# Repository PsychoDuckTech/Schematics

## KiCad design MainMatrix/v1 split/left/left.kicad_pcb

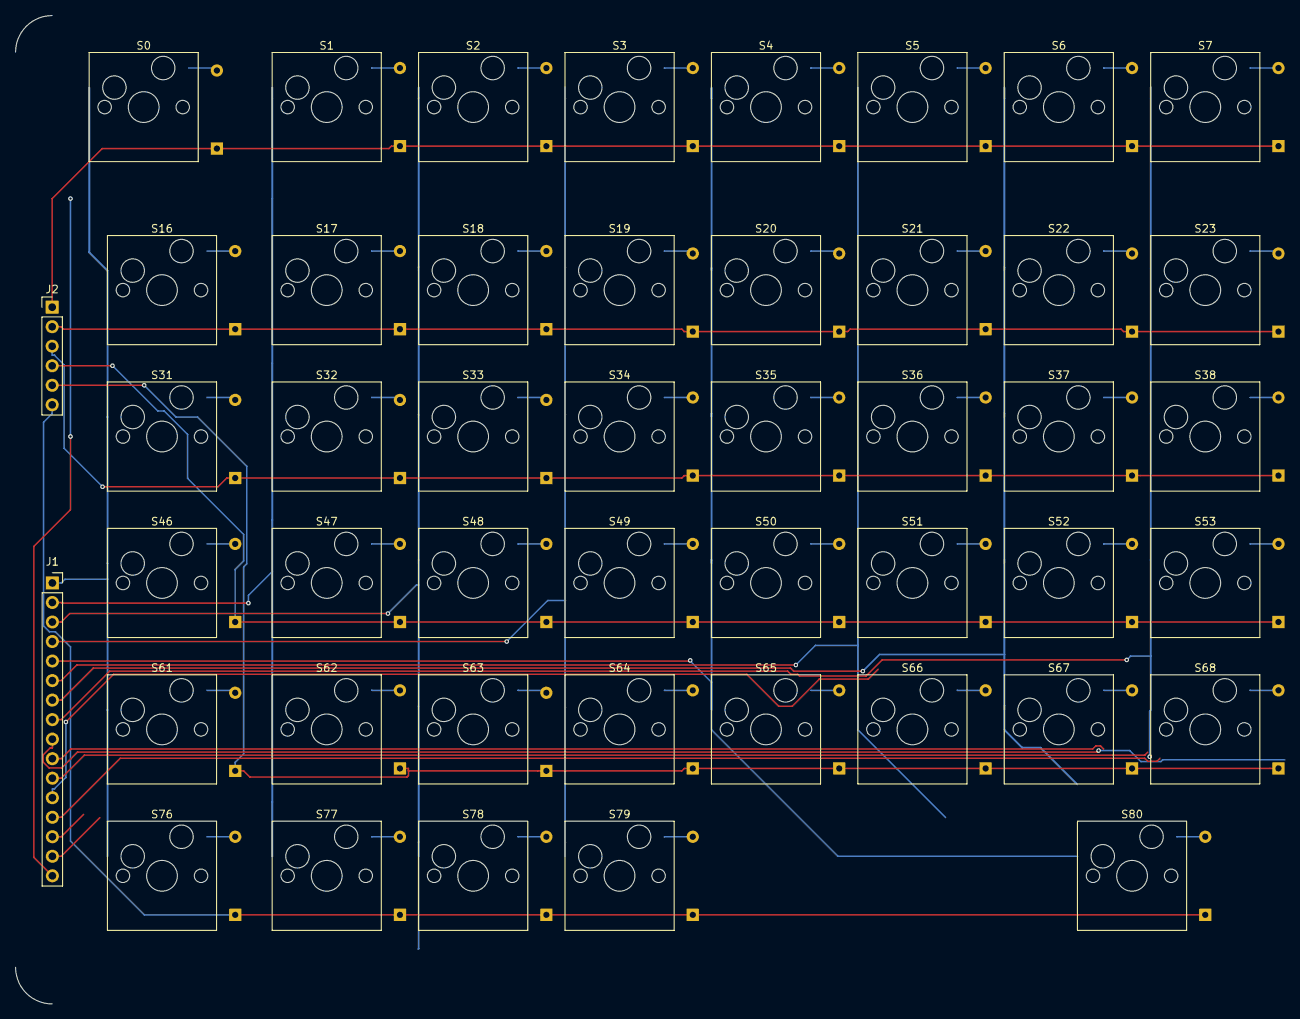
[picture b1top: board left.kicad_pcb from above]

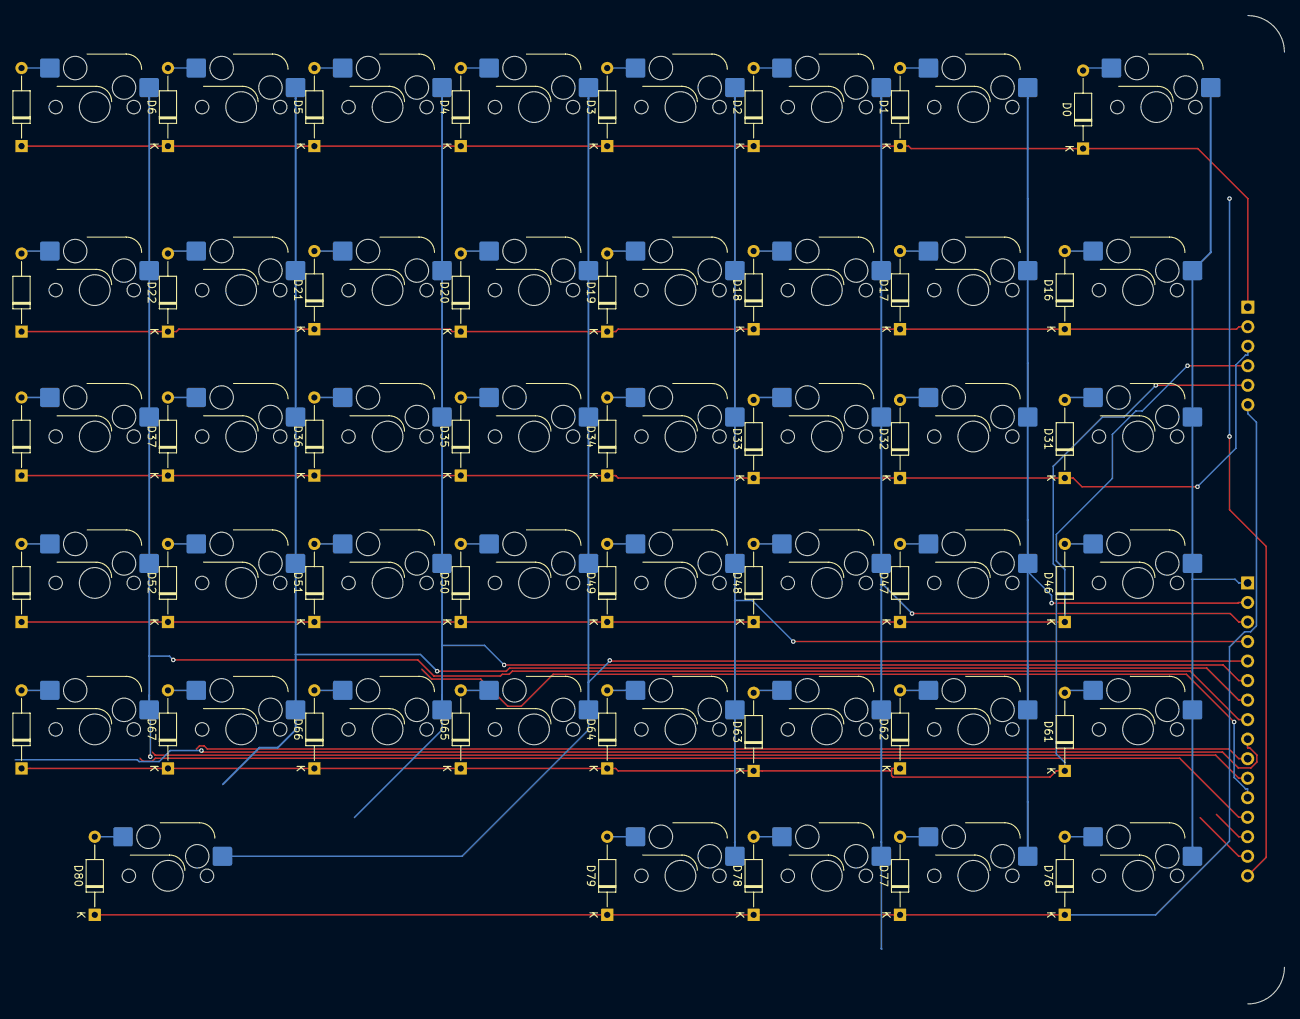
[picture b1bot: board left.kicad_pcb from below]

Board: 2 copper layers, 92 parts (45 on the bottom side), 59 nets.

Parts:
D0, D1, D2, D3, D4, D5, D6, D7, D16, D17, D18, D19, D20, D21, D22, D23, D31, D32, D33, D34, D35, D36, D37, D38, D46, D47, D48, D49, D50, D51, D52, D53, D61, D62, D63, D64, D65, D66, D67, D68, D76, D77, D78, D79, D80: Diode; D_DO-35_SOD27_P10.16mm_Horizontal
J1: Conn_01x16; PinSocket_1x16_P2.54mm_Vertical
J2: Conn_01x06; PinHeader_1x06_P2.54mm_Vertical
S0, S1, S2, S3, S4, S5, S6, S7, S16, S17, S18, S19, S20, S21, S22, S23, S31, S32, S33, S34, S35, S36, S37, S38, S46, S47, S48, S49, S50, S51, S52, S53, S61, S62, S63, S64, S65, S66, S67, S68, S76, S77, S78, S79, S80: Keyswitch; Hotswap_MX_1.00u

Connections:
/Col0: J1.1, S0.1, S16.1, S31.1, S46.1, S61.1, S76.1
/Col1: J1.2, S1.1, S17.1, S32.1, S47.1, S62.1, S77.1
/Col2: J1.3, S2.1, S18.1, S33.1, S48.1, S63.1, S78.1
/Col3: J1.4, S3.1, S19.1, S34.1, S49.1, S64.1, S79.1
/Col4: J1.5, S4.1, S20.1, S35.1, S50.1, S65.1, S80.1
/Col5: J1.6, S5.1, S21.1, S36.1, S51.1, S66.1
/Col6: J1.7, S6.1, S22.1, S37.1, S52.1, S67.1
/Col7: J1.8, S7.1, S23.1, S38.1, S53.1, S68.1
/Row0: D0.1 (K), D1.1 (K), D2.1 (K), D3.1 (K), D4.1 (K), D5.1 (K), D6.1 (K), D7.1 (K), J2.1
/Row1: D16.1 (K), D17.1 (K), D18.1 (K), D19.1 (K), D20.1 (K), D21.1 (K), D22.1 (K), D23.1 (K), J2.2
/Row2: D31.1 (K), D32.1 (K), D33.1 (K), D34.1 (K), D35.1 (K), D36.1 (K), D37.1 (K), D38.1 (K), J2.3
/Row3: D46.1 (K), D47.1 (K), D48.1 (K), D49.1 (K), D50.1 (K), D51.1 (K), D52.1 (K), D53.1 (K), J2.4
/Row4: D61.1 (K), D62.1 (K), D63.1 (K), D64.1 (K), D65.1 (K), D66.1 (K), D67.1 (K), D68.1 (K), J2.5
/Row5: D76.1 (K), D77.1 (K), D78.1 (K), D79.1 (K), D80.1 (K), J2.6
unnamed: D0.2 (A), S0.2
unnamed: D1.2 (A), S1.2
unnamed: D2.2 (A), S2.2
unnamed: D3.2 (A), S3.2
unnamed: D4.2 (A), S4.2
unnamed: D5.2 (A), S5.2
unnamed: D6.2 (A), S6.2
unnamed: D7.2 (A), S7.2
unnamed: D16.2 (A), S16.2
unnamed: D17.2 (A), S17.2
unnamed: D18.2 (A), S18.2
unnamed: D19.2 (A), S19.2
unnamed: D20.2 (A), S20.2
unnamed: D21.2 (A), S21.2
unnamed: D22.2 (A), S22.2
unnamed: D23.2 (A), S23.2
unnamed: D31.2 (A), S31.2
unnamed: D32.2 (A), S32.2
unnamed: D33.2 (A), S33.2
unnamed: D34.2 (A), S34.2
unnamed: D35.2 (A), S35.2
unnamed: D36.2 (A), S36.2
unnamed: D37.2 (A), S37.2
unnamed: D38.2 (A), S38.2
unnamed: D46.2 (A), S46.2
unnamed: D47.2 (A), S47.2
unnamed: D48.2 (A), S48.2
unnamed: D49.2 (A), S49.2
unnamed: D50.2 (A), S50.2
unnamed: D51.2 (A), S51.2
unnamed: D52.2 (A), S52.2
unnamed: D53.2 (A), S53.2
unnamed: D61.2 (A), S61.2
unnamed: D62.2 (A), S62.2
unnamed: D63.2 (A), S63.2
unnamed: D64.2 (A), S64.2
unnamed: D65.2 (A), S65.2
unnamed: D66.2 (A), S66.2
unnamed: D67.2 (A), S67.2
unnamed: D68.2 (A), S68.2
unnamed: D76.2 (A), S76.2
unnamed: D77.2 (A), S77.2
unnamed: D78.2 (A), S78.2
unnamed: D79.2 (A), S79.2
unnamed: D80.2 (A), S80.2

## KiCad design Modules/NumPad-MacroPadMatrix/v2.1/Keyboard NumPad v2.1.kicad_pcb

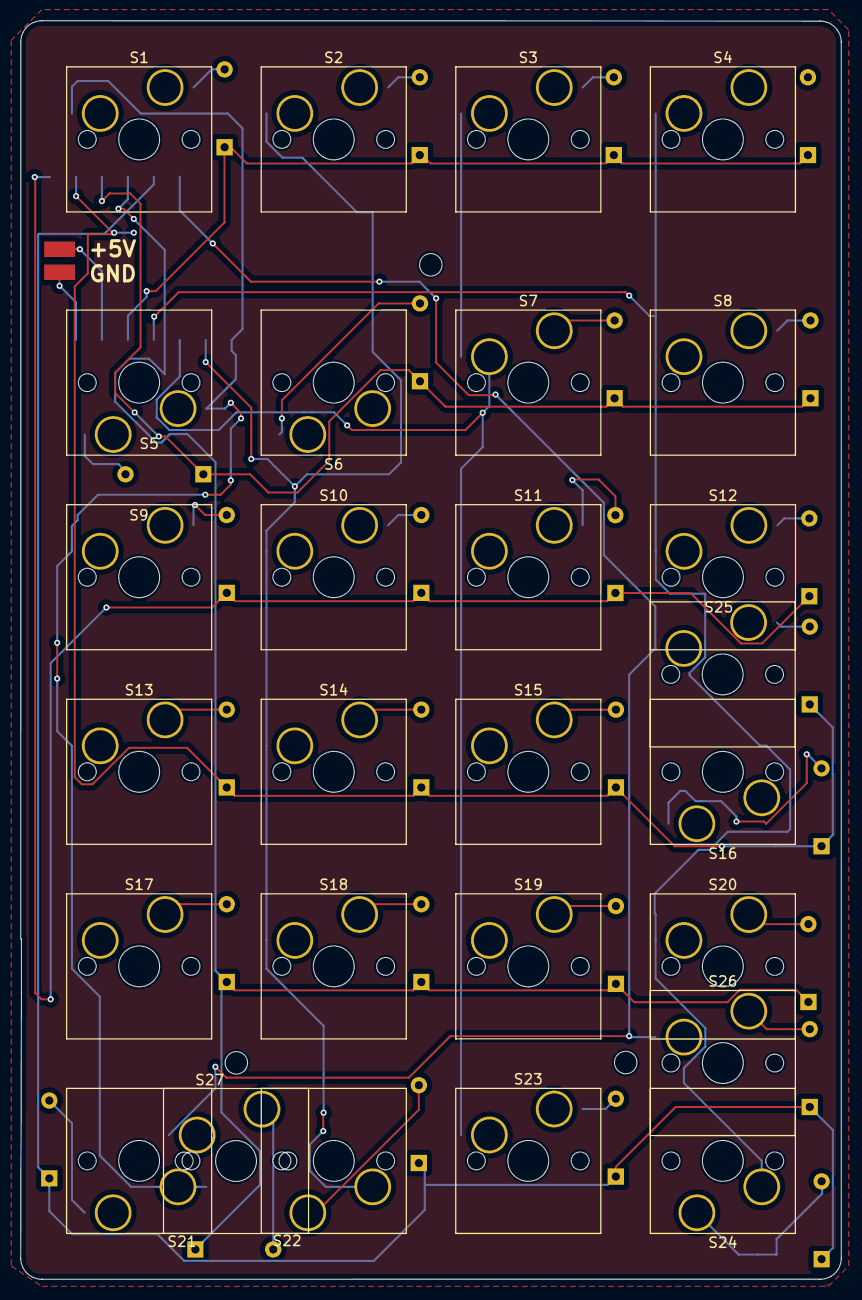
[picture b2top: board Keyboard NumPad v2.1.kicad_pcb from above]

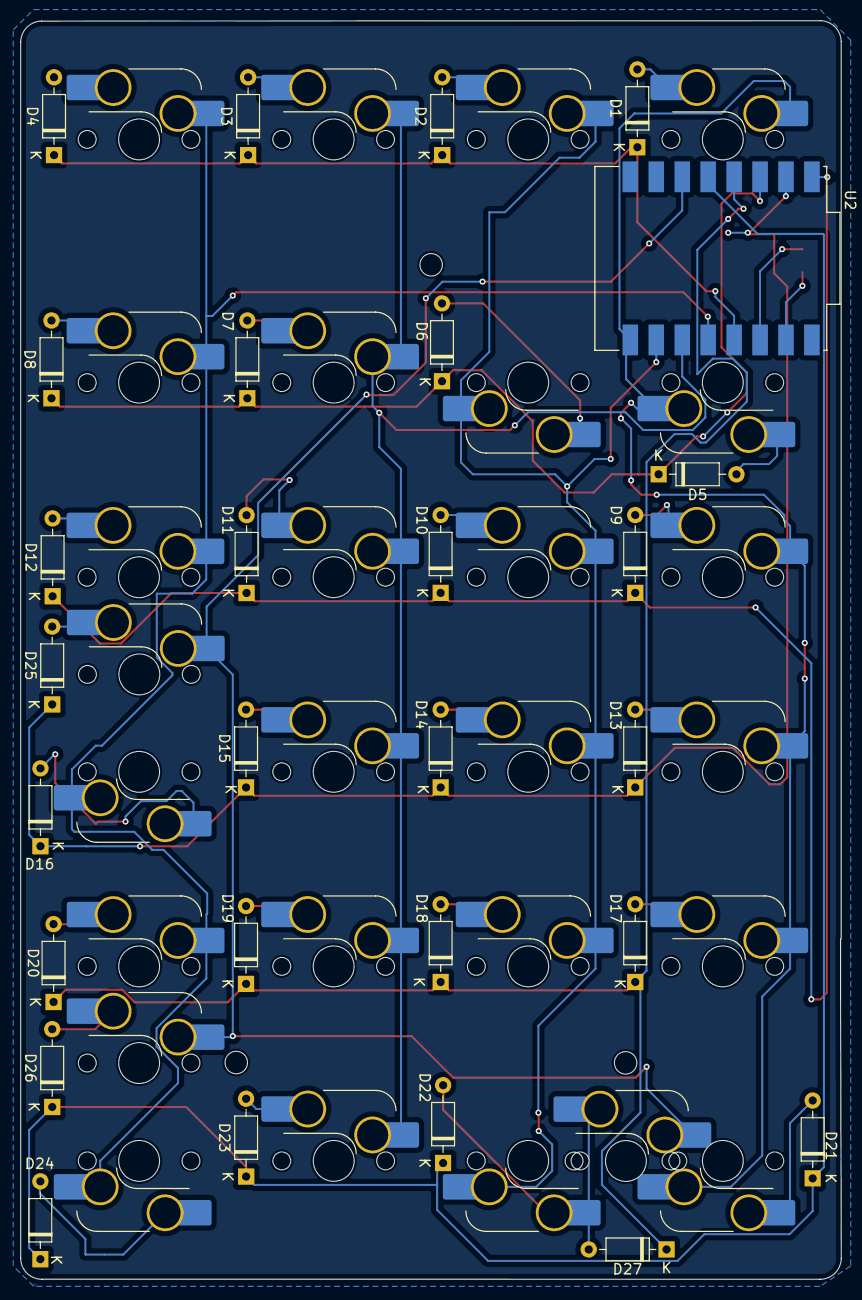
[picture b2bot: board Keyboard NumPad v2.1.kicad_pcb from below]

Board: 2 copper layers, 80.3 x 123.2 mm, 55 parts (28 on the bottom side), 38 nets.

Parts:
D1, D2, D3, D4, D5, D6, D7, D8, D9, D10, D11, D12, D13, D14, D15, D16, D17, D18, D19, D20, D21, D22, D23, D24, D25, D26, D27: Diode; D_DO-35_SOD27_P7.62mm_Horizontal
S1, S2, S3, S4, S5, S6, S7, S8, S9, S10, S11, S12, S13, S14, S15, S16, S17, S18, S19, S20, S21, S22, S23, S24, S25, S26, S27: Keyswitch; Hotswap_MX_Plated_1.00u
U2: ESP32-C3_SUPERMINI_SMD; ESP32-C3_SUPERMINI

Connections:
Coluna 0: S1.1, S5.1, S9.1, S13.1, S17.1, S21.1, U2.0 (GPIO0)
Coluna 1: S2.1, S6.1, S10.1, S14.1, S18.1, S22.1, U2.1 (GPIO1)
Coluna 2: S3.1, S7.1, S11.1, S15.1, S19.1, S23.1, U2.2 (GPIO2)
Coluna 3: S4.1, S8.1, S12.1, S16.1, S20.1, S24.1, U2.3 (GPIO3)
Coluna 4: S25.1, S26.1, S27.1, U2.10 (GPIO10)
Linha 0: D1.1 (K), D2.1 (K), D3.1 (K), D4.1 (K), U2.4 (GPIO4)
Linha 1: D5.1 (K), D6.1 (K), D7.1 (K), D8.1 (K), U2.7 (GPIO7)
Linha 2: D9.1 (K), D10.1 (K), D11.1 (K), D12.1 (K), U2.5 (GPIO5)
Linha 3: D13.1 (K), D14.1 (K), D15.1 (K), D16.1 (K), D25.1 (K), U2.6 (GPIO6)
Linha 4: D17.1 (K), D18.1 (K), D19.1 (K), D20.1 (K), D27.1 (K), U2.8 (GPIO8)
Linha 5: D21.1 (K), D22.1 (K), D23.1 (K), D24.1 (K), D26.1 (K), U2.9 (GPIO9)
unnamed: D1.2 (A), S1.2
unnamed: D2.2 (A), S2.2
unnamed: D3.2 (A), S3.2
unnamed: D4.2 (A), S4.2
unnamed: D5.2 (A), S5.2
unnamed: D6.2 (A), S6.2
unnamed: D7.2 (A), S7.2
unnamed: D8.2 (A), S8.2
unnamed: D9.2 (A), S9.2
unnamed: D10.2 (A), S10.2
unnamed: D11.2 (A), S11.2
unnamed: D12.2 (A), S12.2
unnamed: D13.2 (A), S13.2
unnamed: D14.2 (A), S14.2
unnamed: D15.2 (A), S15.2
unnamed: D16.2 (A), S16.2
unnamed: D17.2 (A), S17.2
unnamed: D18.2 (A), S18.2
unnamed: D19.2 (A), S19.2
unnamed: D20.2 (A), S20.2
unnamed: D21.2 (A), S21.2
unnamed: D22.2 (A), S22.2
unnamed: D23.2 (A), S23.2
unnamed: D24.2 (A), S24.2
unnamed: D25.2 (A), S25.2
unnamed: D26.2 (A), S26.2
unnamed: D27.2 (A), S27.2

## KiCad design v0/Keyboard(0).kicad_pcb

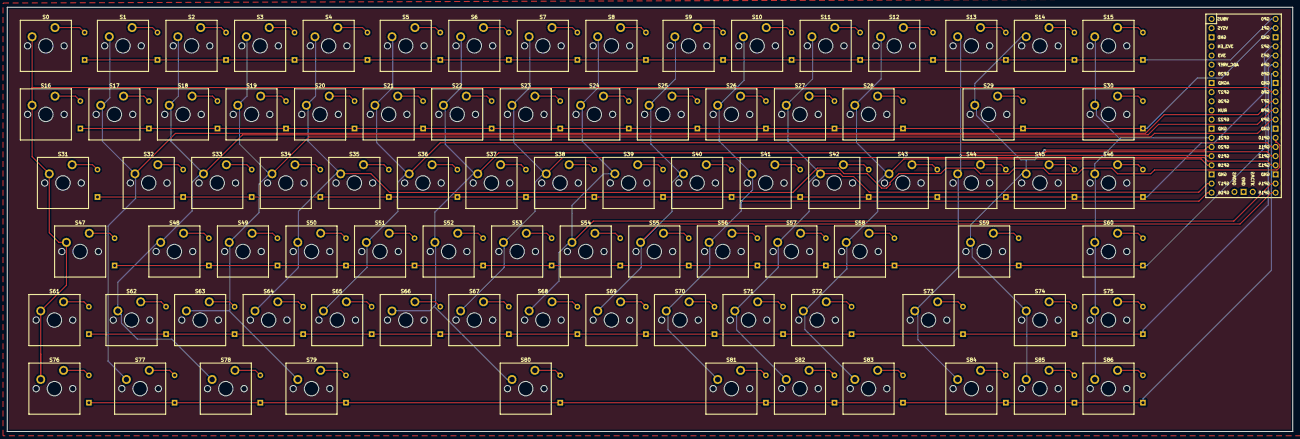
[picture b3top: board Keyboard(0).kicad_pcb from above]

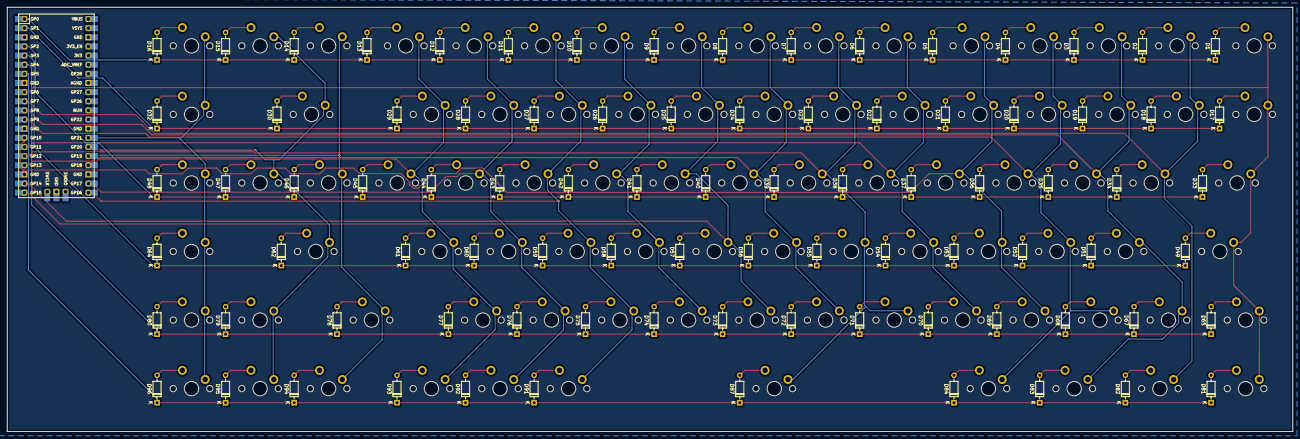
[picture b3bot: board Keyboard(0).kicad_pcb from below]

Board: 2 copper layers, 357.2 x 117.9 mm, 175 parts (88 on the bottom side), 109 nets.

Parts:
D1, D2, D3, D4, D5, D6, D7, D8, D9, D10, D11, D12, D13, D14, D15, D16, D17, D18, D19, D20, D21, D22, D23, D24, D25, D26, D27, D28, D29, D30, D32, D33, D34, D35, D36, D37, D38, D39, D40, D41, D42, D43, D44, D45, D46, D47, D48, D49, D51, D52, D53, D54, D55, D56, D57, D58, D59, D60, D61, D62, D64, D65, D67, D68, D69, D70, D71, D72, D73, D74, D75, D76, D77, D78, D79, D80, D81, D82, D83, D84, D87, D91, D92, D93, D94, D95, D96: Diode; Diode_DO-35
S0, S1, S2, S3, S4, S5, S6, S7, S8, S9, S10, S11, S12, S13, S14, S15, S16, S17, S18, S19, S20, S21, S22, S23, S24, S25, S26, S27, S28, S29, S30, S31, S32, S33, S34, S35, S36, S37, S38, S39, S40, S41, S42, S43, S44, S45, S46, S47, S48, S49, S50, S51, S52, S53, S54, S55, S56, S57, S58, S59, S60, S61, S62, S63, S64, S65, S66, S67, S68, S69, S70, S71, S72, S73, S74, S75, S76, S77, S78, S79, S80, S81, S82, S83, S84, S85, S86: Keyswitch; MX_PCB_1.00u
U1: Raspberry_Pi_Pico

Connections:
Col 00: S0.1, S16.1, S31.1, S47.1, S61.1, S76.1, U1.9 (GPIO6)
Col 01: S1.1, S17.1, S32.1, S77.1, U1.10 (GPIO7)
Col 02: S2.1, S18.1, S33.1, S48.1, S62.1, S78.1, U1.11 (GPIO8)
Col 03: S3.1, S19.1, S34.1, S49.1, S63.1, S79.1, U1.12 (GPIO9)
Col 04: S4.1, S20.1, S35.1, S50.1, S64.1, U1.14 (GPIO10)
Col 05: S5.1, S21.1, S36.1, S51.1, S65.1, U1.15 (GPIO11)
Col 06: S6.1, S22.1, S37.1, S52.1, S66.1, S80.1, U1.16 (GPIO12)
Col 07: S7.1, S23.1, S38.1, S53.1, S67.1, U1.17 (GPIO13)
Col 08: S8.1, S24.1, S39.1, S54.1, S68.1, U1.19 (GPIO14)
Col 09: S9.1, S25.1, S40.1, S55.1, S69.1, U1.20 (GPIO15)
Col 10: S10.1, S26.1, S41.1, S56.1, S70.1, S81.1, U1.21 (GPIO16)
Col 11: S11.1, S27.1, S42.1, S57.1, S71.1, S82.1, U1.22 (GPIO17)
Col 12: S12.1, S28.1, S43.1, S58.1, S72.1, S83.1, U1.24 (GPIO18)
Col 13: S13.1, S44.1, S73.1, S84.1, U1.25 (GPIO19)
Col 14: S14.1, S29.1, S45.1, S59.1, S74.1, S85.1, U1.26 (GPIO20)
Col 15: S15.1, S30.1, S46.1, S60.1, S75.1, S86.1, U1.27 (GPIO21)
unnamed: D1.2 (A), S0.2
unnamed: D2.2 (A), S1.2
unnamed: D3.2 (A), S2.2
unnamed: D4.2 (A), S3.2
unnamed: D5.2 (A), S4.2
unnamed: D6.2 (A), S5.2
unnamed: D7.2 (A), S6.2
unnamed: D8.2 (A), S7.2
unnamed: D9.2 (A), S8.2
unnamed: D10.2 (A), S9.2
unnamed: D11.2 (A), S10.2
unnamed: D12.2 (A), S11.2
unnamed: D13.2 (A), S12.2
unnamed: D14.2 (A), S13.2
unnamed: D15.2 (A), S14.2
unnamed: D16.2 (A), S15.2
unnamed: D17.2 (A), S16.2
unnamed: D18.2 (A), S17.2
unnamed: D19.2 (A), S18.2
unnamed: D20.2 (A), S19.2
unnamed: D21.2 (A), S20.2
unnamed: D22.2 (A), S21.2
unnamed: D23.2 (A), S22.2
unnamed: D24.2 (A), S23.2
unnamed: D25.2 (A), S24.2
unnamed: D26.2 (A), S25.2
unnamed: D27.2 (A), S26.2
unnamed: D28.2 (A), S27.2
unnamed: D29.2 (A), S28.2
unnamed: D30.2 (A), S29.2
unnamed: D32.2 (A), S30.2
unnamed: D33.2 (A), S31.2
unnamed: D34.2 (A), S32.2
unnamed: D35.2 (A), S33.2
unnamed: D36.2 (A), S34.2
unnamed: D37.2 (A), S35.2
unnamed: D38.2 (A), S36.2
unnamed: D39.2 (A), S37.2
unnamed: D40.2 (A), S38.2
unnamed: D41.2 (A), S39.2
unnamed: D42.2 (A), S40.2
unnamed: D43.2 (A), S41.2
unnamed: D44.2 (A), S42.2
unnamed: D45.2 (A), S43.2
unnamed: D46.2 (A), S44.2
unnamed: D47.2 (A), S45.2
unnamed: D48.2 (A), S46.2
unnamed: D49.2 (A), S47.2
unnamed: D51.2 (A), S48.2
unnamed: D52.2 (A), S49.2
unnamed: D53.2 (A), S50.2
unnamed: D54.2 (A), S51.2
unnamed: D55.2 (A), S52.2
unnamed: D56.2 (A), S53.2
unnamed: D57.2 (A), S54.2
unnamed: D58.2 (A), S55.2
unnamed: D59.2 (A), S56.2
unnamed: D60.2 (A), S57.2
unnamed: D61.2 (A), S58.2
unnamed: D62.2 (A), S59.2
unnamed: D64.2 (A), S60.2
unnamed: D65.2 (A), S61.2
unnamed: D67.2 (A), S62.2
unnamed: D68.2 (A), S63.2
unnamed: D69.2 (A), S64.2
unnamed: D70.2 (A), S65.2
unnamed: D71.2 (A), S66.2
unnamed: D72.2 (A), S67.2
unnamed: D73.2 (A), S68.2
unnamed: D74.2 (A), S69.2
unnamed: D75.2 (A), S70.2
unnamed: D76.2 (A), S71.2
unnamed: D77.2 (A), S72.2
unnamed: D78.2 (A), S73.2
unnamed: D79.2 (A), S74.2
unnamed: D80.2 (A), S75.2
unnamed: D81.2 (A), S76.2
unnamed: D82.2 (A), S77.2
unnamed: D83.2 (A), S78.2
unnamed: D84.2 (A), S79.2
unnamed: D87.2 (A), S80.2
unnamed: D91.2 (A), S81.2
unnamed: D92.2 (A), S82.2
unnamed: D93.2 (A), S83.2
unnamed: D94.2 (A), S84.2
unnamed: D95.2 (A), S85.2
unnamed: D96.2 (A), S86.2
Row 0: D1.1 (K), D2.1 (K), D3.1 (K), D4.1 (K), D5.1 (K), D6.1 (K), D7.1 (K), D8.1 (K), D9.1 (K), D10.1 (K), D11.1 (K), D12.1 (K), D13.1 (K), D14.1 (K), D15.1 (K), D16.1 (K), U1.1 (GPIO0)
Row 1: D17.1 (K), D18.1 (K), D19.1 (K), D20.1 (K), D21.1 (K), D22.1 (K), D23.1 (K), D24.1 (K), D25.1 (K), D26.1 (K), D27.1 (K), D28.1 (K), D29.1 (K), D30.1 (K), D32.1 (K), U1.2 (GPIO1)
Row 2: D33.1 (K), D34.1 (K), D35.1 (K), D36.1 (K), D37.1 (K), D38.1 (K), D39.1 (K), D40.1 (K), D41.1 (K), D42.1 (K), D43.1 (K), D44.1 (K), D45.1 (K), D46.1 (K), D47.1 (K), D48.1 (K), U1.4 (GPIO2)
Row 3: D49.1 (K), D51.1 (K), D52.1 (K), D53.1 (K), D54.1 (K), D55.1 (K), D56.1 (K), D57.1 (K), D58.1 (K), D59.1 (K), D60.1 (K), D61.1 (K), D62.1 (K), D64.1 (K), U1.5 (GPIO3)
Row 4: D65.1 (K), D67.1 (K), D68.1 (K), D69.1 (K), D70.1 (K), D71.1 (K), D72.1 (K), D73.1 (K), D74.1 (K), D75.1 (K), D76.1 (K), D77.1 (K), D78.1 (K), D79.1 (K), D80.1 (K), U1.6 (GPIO4)
Row 5: D81.1 (K), D82.1 (K), D83.1 (K), D84.1 (K), D87.1 (K), D91.1 (K), D92.1 (K), D93.1 (K), D94.1 (K), D95.1 (K), D96.1 (K), U1.7 (GPIO5)

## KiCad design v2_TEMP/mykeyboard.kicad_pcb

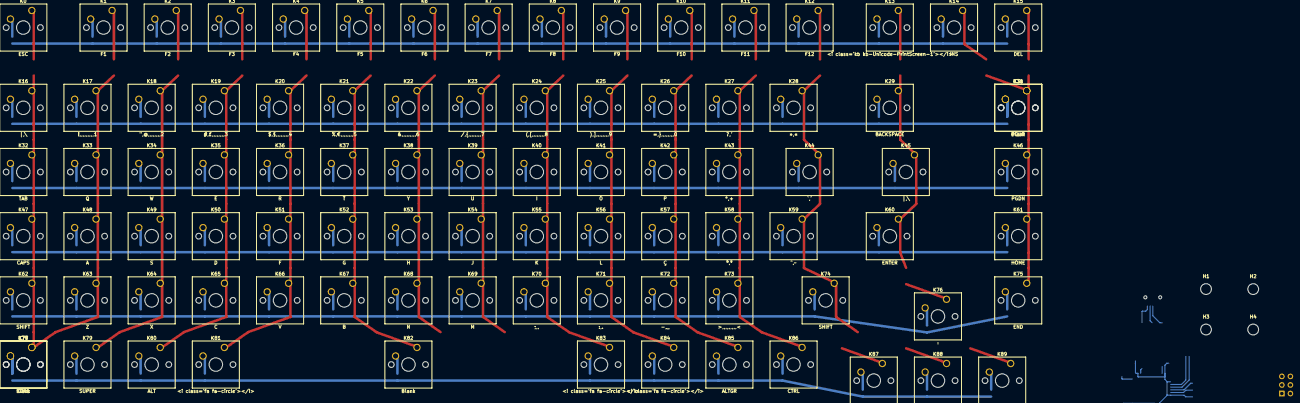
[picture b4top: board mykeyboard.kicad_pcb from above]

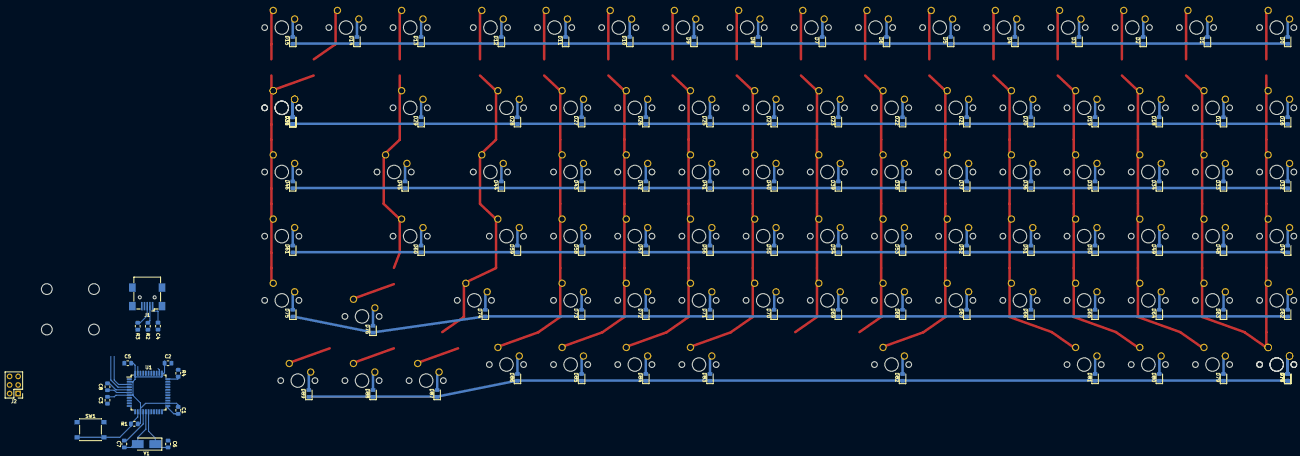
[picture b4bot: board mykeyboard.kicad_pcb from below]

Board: 2 copper layers, 201 parts (107 on the bottom side), 123 nets.

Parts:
C1, C2, C3, C4: 0.1u; C_0805_2012Metric_Pad1.15x1.40mm_HandSolder
C5: 4.7u; C_0805_2012Metric_Pad1.15x1.40mm_HandSolder
C6, C7: 22p; C_0805_2012Metric_Pad1.15x1.40mm_HandSolder
C8: 1u; C_0805_2012Metric_Pad1.15x1.40mm_HandSolder
D0, D1, D2, D3, D4, D5, D6, D7, D8, D9, D10, D11, D12, D13, D14, D15, D16, D17, D18, D19, D20, D21, D22, D23, D24, D25, D26, D27, D28, D29, D30, D31, D32, D33, D34, D35, D36, D37, D38, D39, D40, D41, D42, D43, D44, D45, D46, D47, D48, D49, D50, D51, D52, D53, D54, D55, D56, D57, D58, D59, D60, D61, D62, D63, D64, D65, D66, D67, D68, D69, D70, D71, D72, D73, D74, D75, D76, D77, D78, D79, D80, D81, D82, D83, D84, D85, D86, D87, D88, D89: D; D_0805_2012Metric_Pad1.15x1.40mm_HandSolder
H1, H2, H3, H4: MountingHole; MountingHole_3.2mm_M3_DIN965
J1: USB_mini_micro_B; USB_Mini-B_Wuerth_65100516121_Horizontal
J2: Conn_02x03_Odd_Even; PinHeader_2x03_P2.54mm_Vertical
K0: ESC; SW_Cherry_MX_1.00u_PCB
K1: F1; SW_Cherry_MX_1.00u_PCB
K2: F2; SW_Cherry_MX_1.00u_PCB
K3: F3; SW_Cherry_MX_1.00u_PCB
K4: F4; SW_Cherry_MX_1.00u_PCB
K5: F5; SW_Cherry_MX_1.00u_PCB
K6: F6; SW_Cherry_MX_1.00u_PCB
K7: F7; SW_Cherry_MX_1.00u_PCB
K8: F8; SW_Cherry_MX_1.00u_PCB
K9: F9; SW_Cherry_MX_1.00u_PCB
K10: F10; SW_Cherry_MX_1.00u_PCB
K11: F11; SW_Cherry_MX_1.00u_PCB
K12: F12; SW_Cherry_MX_1.00u_PCB
K13: <i class='kb kb-Unicode-PrintScreen-1'></i>; SW_Cherry_MX_1.00u_PCB
K14: INS; SW_Cherry_MX_1.00u_PCB
K15: DEL; SW_Cherry_MX_1.00u_PCB
K16: |,\; SW_Cherry_MX_1.00u_PCB
K17: !,,,,,,,,,1; SW_Cherry_MX_1.00u_PCB
K18: ",@,,,,,,,,2; SW_Cherry_MX_1.00u_PCB
K19: #,£,,,,,,,,3; SW_Cherry_MX_1.00u_PCB
K20: $,§,,,,,,,,4; SW_Cherry_MX_1.00u_PCB
K21: %,€,,,,,,,,5; SW_Cherry_MX_1.00u_PCB
K22: &,,,,,,,,,6; SW_Cherry_MX_1.00u_PCB
K23: /,{,,,,,,,,7; SW_Cherry_MX_1.00u_PCB
K24: (,[,,,,,,,,8; SW_Cherry_MX_1.00u_PCB
K25: ),],,,,,,,,9; SW_Cherry_MX_1.00u_PCB
K26: =,},,,,,,,,0; SW_Cherry_MX_1.00u_PCB
K27: ?,'; SW_Cherry_MX_1.00u_PCB
K28: »,«; SW_Cherry_MX_1.00u_PCB
K29: BACKSPACE; SW_Cherry_MX_2.00u_PCB
K30, K77: Blank; SW_Cherry_MX_1.00u_PCB
K31: PGUP; SW_Cherry_MX_1.00u_PCB
K32: TAB; SW_Cherry_MX_1.00u_PCB
K33: Q; SW_Cherry_MX_1.00u_PCB
K34: W; SW_Cherry_MX_1.00u_PCB
K35: E; SW_Cherry_MX_1.00u_PCB
K36: R; SW_Cherry_MX_1.00u_PCB
K37: T; SW_Cherry_MX_1.00u_PCB
K38: Y; SW_Cherry_MX_1.00u_PCB
K39: U; SW_Cherry_MX_1.00u_PCB
K40: I; SW_Cherry_MX_1.00u_PCB
K41: O; SW_Cherry_MX_1.00u_PCB
K42: P; SW_Cherry_MX_1.00u_PCB
K43: *,+; SW_Cherry_MX_1.00u_PCB
K44: `,´; SW_Cherry_MX_1.50u_PCB
K45: |,\; SW_Cherry_MX_1.50u_PCB
K46: PGDN; SW_Cherry_MX_1.00u_PCB
K47: CAPS; SW_Cherry_MX_1.00u_PCB
K48: A; SW_Cherry_MX_1.00u_PCB
K49: S; SW_Cherry_MX_1.00u_PCB
K50: D; SW_Cherry_MX_1.00u_PCB
K51: F; SW_Cherry_MX_1.00u_PCB
K52: G; SW_Cherry_MX_1.00u_PCB
K53: H; SW_Cherry_MX_1.00u_PCB
K54: J; SW_Cherry_MX_1.00u_PCB
K55: K; SW_Cherry_MX_1.00u_PCB
K56: L; SW_Cherry_MX_1.00u_PCB
K57: Ç; SW_Cherry_MX_1.00u_PCB
K58: ª,º; SW_Cherry_MX_1.00u_PCB
K59: ^,~~; SW_Cherry_MX_1.00u_PCB
K60: ENTER; SW_Cherry_MX_2.00u_PCB
K61: HOME; SW_Cherry_MX_1.00u_PCB
K62: SHIFT; SW_Cherry_MX_1.00u_PCB
K63: Z; SW_Cherry_MX_1.00u_PCB
K64: X; SW_Cherry_MX_1.00u_PCB
K65: C; SW_Cherry_MX_1.00u_PCB
K66: V; SW_Cherry_MX_1.00u_PCB
K67: B; SW_Cherry_MX_1.00u_PCB
K68: N; SW_Cherry_MX_1.00u_PCB
K69: M; SW_Cherry_MX_1.00u_PCB
K70: ;,,; SW_Cherry_MX_1.00u_PCB
K71: :,.; SW_Cherry_MX_1.00u_PCB
K72: -,_; SW_Cherry_MX_1.00u_PCB
K73: >,,,,,,,,,<; SW_Cherry_MX_1.00u_PCB
K74: SHIFT; SW_Cherry_MX_2.00u_PCB
K75: END; SW_Cherry_MX_1.00u_PCB
K76: ∧; SW_Cherry_MX_1.00u_PCB
K78, K86: CTRL; SW_Cherry_MX_1.00u_PCB
K79: SUPER; SW_Cherry_MX_1.00u_PCB
K80: ALT; SW_Cherry_MX_1.00u_PCB
K81, K83, K84: <i class='fa fa-circle'></i>; SW_Cherry_MX_1.00u_PCB
K82: Blank; SW_Cherry_MX_2.75u_PCB
K85: ALTGR; SW_Cherry_MX_1.00u_PCB
K87: <; SW_Cherry_MX_1.00u_PCB
K88: ∨; SW_Cherry_MX_1.00u_PCB
K89: >; SW_Cherry_MX_1.00u_PCB
R1, R4: 10k; R_0805_2012Metric_Pad1.15x1.40mm_HandSolder
R2, R3: 22R; R_0805_2012Metric_Pad1.15x1.40mm_HandSolder
SW1: SW_Push; SW_Push_1P1T_NO_6x6mm_H9.5mm
U1: ATmega32U4-AU; TQFP-44_10x10mm_P0.8mm
Y1: Crystal; Crystal_SMD_5032-2Pin_5.0x3.2mm_HandSoldering

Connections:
/Col_0: K0.1, K16.1, K32.1, K47.1, K62.1, K77.1, U1.32
/Col_1: K1.1, K17.1, K33.1, K48.1, K63.1, K78.1, U1.31
/Col_2: K2.1, K18.1, K34.1, K49.1, K64.1, K79.1, U1.30
/Col_3: K3.1, K19.1, K35.1, K50.1, K65.1, K80.1, U1.29
/Col_4: K4.1, K20.1, K36.1, K51.1, K66.1, K81.1, U1.28
/Col_5: K5.1, K21.1, K37.1, K52.1, K67.1, K82.1, U1.27
/Col_6: K6.1, K22.1, K38.1, K53.1, K68.1, K83.1, U1.26
/Col_7: K7.1, K23.1, K39.1, K54.1, K69.1, K84.1, U1.25
/Col_8: K8.1, K24.1, K40.1, K55.1, K70.1, K85.1, U1.36
/Col_9: K9.1, K25.1, K41.1, K56.1, K71.1, K86.1, U1.37
/Col_10: K10.1, K26.1, K42.1, K57.1, K72.1, K87.1, U1.38
/Col_11: K11.1, K27.1, K43.1, K58.1, K73.1, K88.1, U1.39
/Col_12: K12.1, K28.1, K44.1, K59.1, K74.1, K89.1, U1.40
/Col_13: K13.1, K29.1, K45.1, K60.1, K76.1, U1.41
/Col_14: K14.1, K30.1, K46.1, K61.1, K75.1, U1.22
/Col_15: K15.1, K31.1, U1.19
/Row_0: D0.1, D1.1, D2.1, D3.1, D4.1, D5.1, D6.1, D7.1, D8.1, D9.1, D10.1, D11.1, D12.1, D13.1, D14.1, D15.1, U1.18
/Row_1: D16.1, D17.1, D18.1, D19.1, D20.1, D21.1, D22.1, D23.1, D24.1, D25.1, D26.1, D27.1, D28.1, D29.1, D30.1, D31.1, U1.12
/Row_2: D32.1, D33.1, D34.1, D35.1, D36.1, D37.1, D38.1, D39.1, D40.1, D41.1, D42.1, D43.1, D44.1, D45.1, D46.1, J2.2, U1.11
/Row_3: D47.1, D48.1, D49.1, D50.1, D51.1, D52.1, D53.1, D54.1, D55.1, D56.1, D57.1, D58.1, D59.1, D60.1, D61.1, J2.4, U1.10
/Row_4: D62.1, D63.1, D64.1, D65.1, D66.1, D67.1, D68.1, D69.1, D70.1, D71.1, D72.1, D73.1, D74.1, D75.1, D76.1, J2.3, U1.9
/Row_5: D77.1, D78.1, D79.1, D80.1, D81.1, D82.1, D83.1, D84.1, D85.1, D86.1, D87.1, D88.1, D89.1, U1.8
GND: C1.2, C2.2, C3.2, C4.2, C5.2, C6.2, C7.2, C8.2, J1.5, J1.6, J2.5, R4.1, SW1.1, U1.5, U1.15, U1.23, U1.35, U1.43
unnamed: C6.1, U1.17, Y1.1
unnamed: C7.1, U1.16, Y1.2
unnamed: C8.1, U1.6
unnamed: D0.2, K0.2
unnamed: D1.2, K1.2
unnamed: D2.2, K2.2
unnamed: D3.2, K3.2
unnamed: D4.2, K4.2
unnamed: D5.2, K5.2
unnamed: D6.2, K6.2
unnamed: D7.2, K7.2
unnamed: D8.2, K8.2
unnamed: D9.2, K9.2
unnamed: D10.2, K10.2
unnamed: D11.2, K11.2
unnamed: D12.2, K12.2
unnamed: D13.2, K13.2
unnamed: D14.2, K14.2
unnamed: D15.2, K15.2
unnamed: D16.2, K16.2
unnamed: D17.2, K17.2
unnamed: D18.2, K18.2
unnamed: D19.2, K19.2
unnamed: D20.2, K20.2
unnamed: D21.2, K21.2
unnamed: D22.2, K22.2
unnamed: D23.2, K23.2
unnamed: D24.2, K24.2
unnamed: D25.2, K25.2
unnamed: D26.2, K26.2
unnamed: D27.2, K27.2
unnamed: D28.2, K28.2
unnamed: D29.2, K29.2
unnamed: D30.2, K30.2
unnamed: D31.2, K31.2
unnamed: D32.2, K32.2
unnamed: D33.2, K33.2
unnamed: D34.2, K34.2
unnamed: D35.2, K35.2
unnamed: D36.2, K36.2
unnamed: D37.2, K37.2
unnamed: D38.2, K38.2
unnamed: D39.2, K39.2
unnamed: D40.2, K40.2
unnamed: D41.2, K41.2
unnamed: D42.2, K42.2
unnamed: D43.2, K43.2
unnamed: D44.2, K44.2
unnamed: D45.2, K45.2
unnamed: D46.2, K46.2
unnamed: D47.2, K47.2
unnamed: D48.2, K48.2
unnamed: D49.2, K49.2
unnamed: D50.2, K50.2
unnamed: D51.2, K51.2
unnamed: D52.2, K52.2
unnamed: D53.2, K53.2
unnamed: D54.2, K54.2
unnamed: D55.2, K55.2
unnamed: D56.2, K56.2
unnamed: D57.2, K57.2
unnamed: D58.2, K58.2
unnamed: D59.2, K59.2
unnamed: D60.2, K60.2
unnamed: D61.2, K61.2
unnamed: D62.2, K62.2
unnamed: D63.2, K63.2
unnamed: D64.2, K64.2
unnamed: D65.2, K65.2
unnamed: D66.2, K66.2
unnamed: D67.2, K67.2
unnamed: D68.2, K68.2
unnamed: D69.2, K69.2
unnamed: D70.2, K70.2
unnamed: D71.2, K71.2
unnamed: D72.2, K72.2
unnamed: D73.2, K73.2
unnamed: D74.2, K74.2
unnamed: D75.2, K75.2
unnamed: D76.2, K76.2
unnamed: D77.2, K77.2
unnamed: D78.2, K78.2
unnamed: D79.2, K79.2
unnamed: D80.2, K80.2
unnamed: D81.2, K81.2
unnamed: D82.2, K82.2
unnamed: D83.2, K83.2
unnamed: D84.2, K84.2
unnamed: D85.2, K85.2
unnamed: D86.2, K86.2
unnamed: D87.2, K87.2
unnamed: D88.2, K88.2
unnamed: D89.2, K89.2
unnamed: J1.2, R2.2
unnamed: J1.3, R3.2
unnamed: R1.1, SW1.2, U1.13
unnamed: R2.1, U1.4
unnamed: R3.1, U1.3
unnamed: R4.2, U1.33
VCC: C1.1, C2.1, C3.1, C4.1, C5.1, J1.1, J2.1, R1.2, U1.2, U1.7, U1.14, U1.24, U1.34, U1.44
